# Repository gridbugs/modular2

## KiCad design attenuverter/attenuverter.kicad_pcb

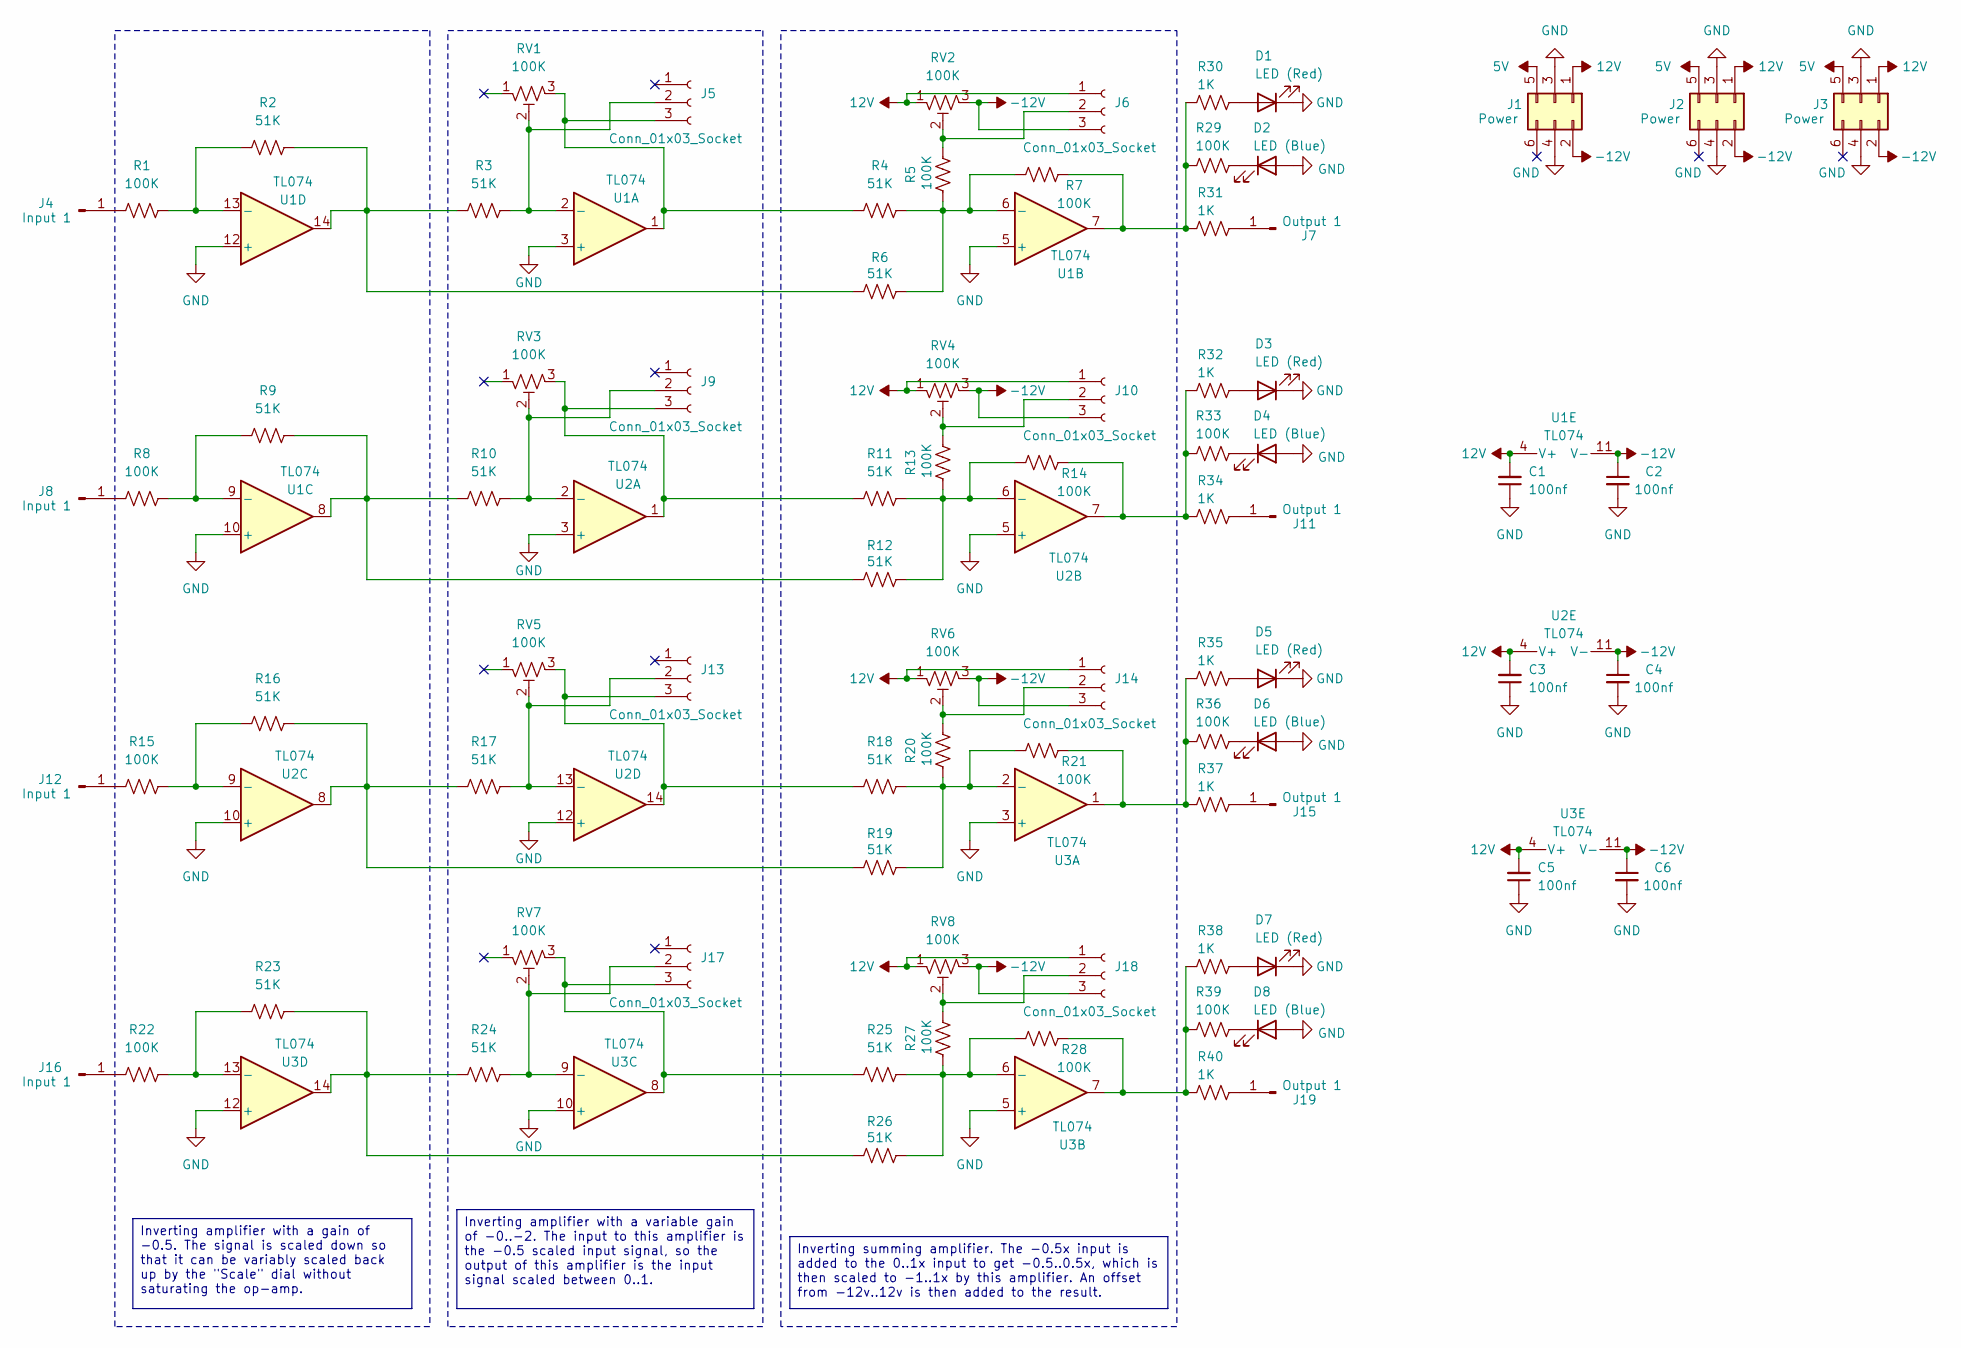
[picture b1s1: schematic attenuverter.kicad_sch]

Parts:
C1, C2, C3, C4, C5, C6: 100nf; C_Disc_D4.3mm_W1.9mm_P5.00mm
D1, D3, D5, D7: LED (Red); LED_D5.0mm
D2, D4, D6, D8: LED (Blue); LED_D5.0mm
J1, J2, J3: Power; IDC-Header_2x03_P2.54mm_Vertical
J4, J8, J12, J16: Input 1; banana-jack
J5, J6, J9, J10, J13, J14, J17, J18: Conn_01x03_Socket; pot
J7, J11, J15, J19: Output 1; banana-jack
R1, R5, R7, R8, R13, R14, R15, R20, R21, R22, R27, R28, R29, R33, R36, R39: 100K; R_Axial_DIN0207_L6.3mm_D2.5mm_P10.16mm_Horizontal
R2, R3, R4, R6, R9, R10, R11, R12, R16, R17, R18, R19, R23, R24, R25, R26: 51K; R_Axial_DIN0207_L6.3mm_D2.5mm_P10.16mm_Horizontal
R30, R31, R32, R34, R35, R37, R38, R40: 1K; R_Axial_DIN0207_L6.3mm_D2.5mm_P10.16mm_Horizontal
RV1, RV2, RV3, RV4, RV5, RV6, RV7, RV8: 100K; pot-socket
U1, U2, U3: TL074; DIP-14_W7.62mm_Socket

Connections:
5V: J1.5, J2.5, J3.5
12V: C1.2, C3.2, C5.2, J1.1, J2.1, J3.1, J6.1, J10.1, J14.1, J18.1, RV2.1, RV4.1, RV6.1, RV8.1, U1.4 (V+), U2.4 (V+), U3.4 (V+)
-12V: C2.1, C4.1, C6.1, J1.2, J2.2, J3.2, J6.3, J10.3, J14.3, J18.3, RV2.3, RV4.3, RV6.3, RV8.3, U1.11 (V-), U2.11 (V-), U3.11 (V-)
GND: C1.1, C2.2, C3.1, C4.2, C5.1, C6.2, D1.1 (K), D2.2 (A), D3.1 (K), D4.2 (A), D5.1 (K), D6.2 (A), D7.1 (K), D8.2 (A), J1.3, J1.4, J2.3, J2.4, J3.3, J3.4, U1.3 (+), U1.5 (+), U1.10 (+), U1.12 (+), U2.3 (+), U2.5 (+), U2.10 (+), U2.12 (+), U3.3 (+), U3.5 (+), U3.10 (+), U3.12 (+)
unnamed: D1.2 (A), R30.1
unnamed: D2.1 (K), R29.2
unnamed: D3.2 (A), R32.1
unnamed: D4.1 (K), R33.2
unnamed: D5.2 (A), R35.1
unnamed: D6.1 (K), R36.2
unnamed: D7.2 (A), R38.1
unnamed: D8.1 (K), R39.2
unnamed: J4.1, R1.1
unnamed: J5.2, R3.2, RV1.2, U1.2 (-)
unnamed: J5.3, R4.1, RV1.3, U1.1
unnamed: J6.2, R5.2, RV2.2
unnamed: J7.1, R31.1
unnamed: J8.1, R8.1
unnamed: J9.2, R10.2, RV3.2, U2.2 (-)
unnamed: J9.3, R11.1, RV3.3, U2.1
unnamed: J10.2, R13.2, RV4.2
unnamed: J11.1, R34.1
unnamed: J12.1, R15.1
unnamed: J13.2, R17.2, RV5.2, U2.13 (-)
unnamed: J13.3, R18.1, RV5.3, U2.14
unnamed: J14.2, R20.2, RV6.2
unnamed: J15.1, R37.1
unnamed: J16.1, R22.1
unnamed: J17.2, R24.2, RV7.2, U3.9 (-)
unnamed: J17.3, R25.1, RV7.3, U3.8
unnamed: J18.2, R27.2, RV8.2
unnamed: J19.1, R40.1
unnamed: R2.2, R3.1, R6.1, U1.14
unnamed: R9.2, R10.1, R12.1, U1.8
unnamed: R14.2, R32.2, R33.1, R34.2, U2.7
unnamed: R16.2, R17.1, R19.1, U2.8
unnamed: R21.2, R35.2, R36.1, R37.2, U3.1
unnamed: R23.2, R24.1, R26.1, U3.14
unnamed: R28.2, R38.2, R39.1, R40.2, U3.7
unnamed: R7.2, R29.1, R30.2, R31.2, U1.7
unnamed: R4.2, R5.1, R6.2, R7.1, U1.6 (-)
unnamed: R8.2, R9.1, U1.9 (-)
unnamed: R1.2, R2.1, U1.13 (-)
unnamed: R11.2, R12.2, R13.1, R14.1, U2.6 (-)
unnamed: R15.2, R16.1, U2.9 (-)
unnamed: R18.2, R19.2, R20.1, R21.1, U3.2 (-)
unnamed: R25.2, R26.2, R27.1, R28.1, U3.6 (-)
unnamed: R22.2, R23.1, U3.13 (-)

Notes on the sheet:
Inverting amplifier with a variable gain of -0..-2. The input to this amplifier is the -0.5 scaled input signal, so the output of this amplifier is the input signal scaled between 0..1.
Inverting amplifier with a gain of -0.5. The signal is scaled down so that it can be variably scaled back up by the "Scale" dial without saturating the op-amp.
Inverting summing amplifier. The -0.5x input is added to the 0..1x input to get -0.5..0.5x, which is then scaled to -1..1x by this amplifier. An offset from -12v..12v is then added to the result.

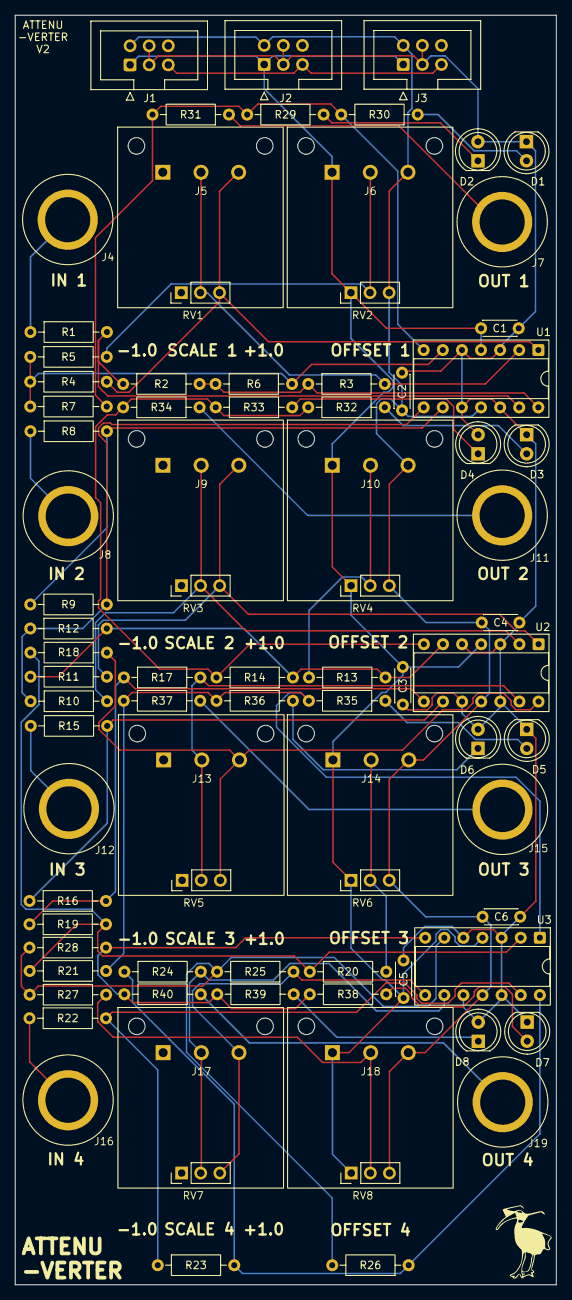
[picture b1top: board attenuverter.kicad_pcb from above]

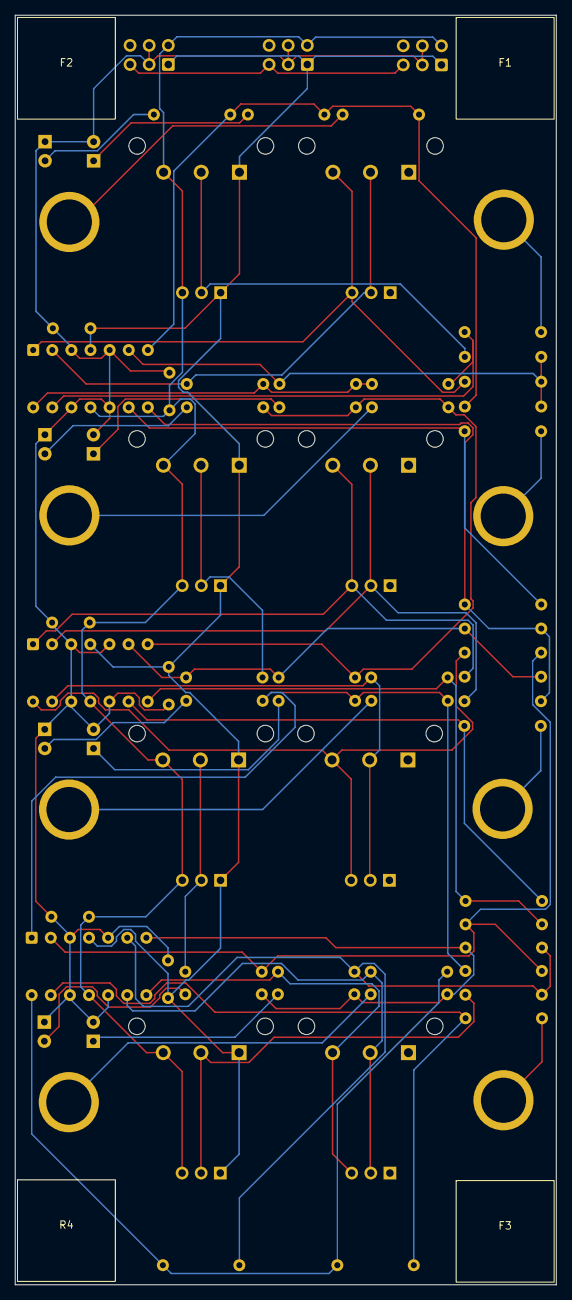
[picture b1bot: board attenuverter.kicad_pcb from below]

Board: 2 copper layers, 71.9 x 168.7 mm, 88 parts (4 on the bottom side), 48 nets.

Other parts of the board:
F1, F2, F3: foot
R4#2: foot

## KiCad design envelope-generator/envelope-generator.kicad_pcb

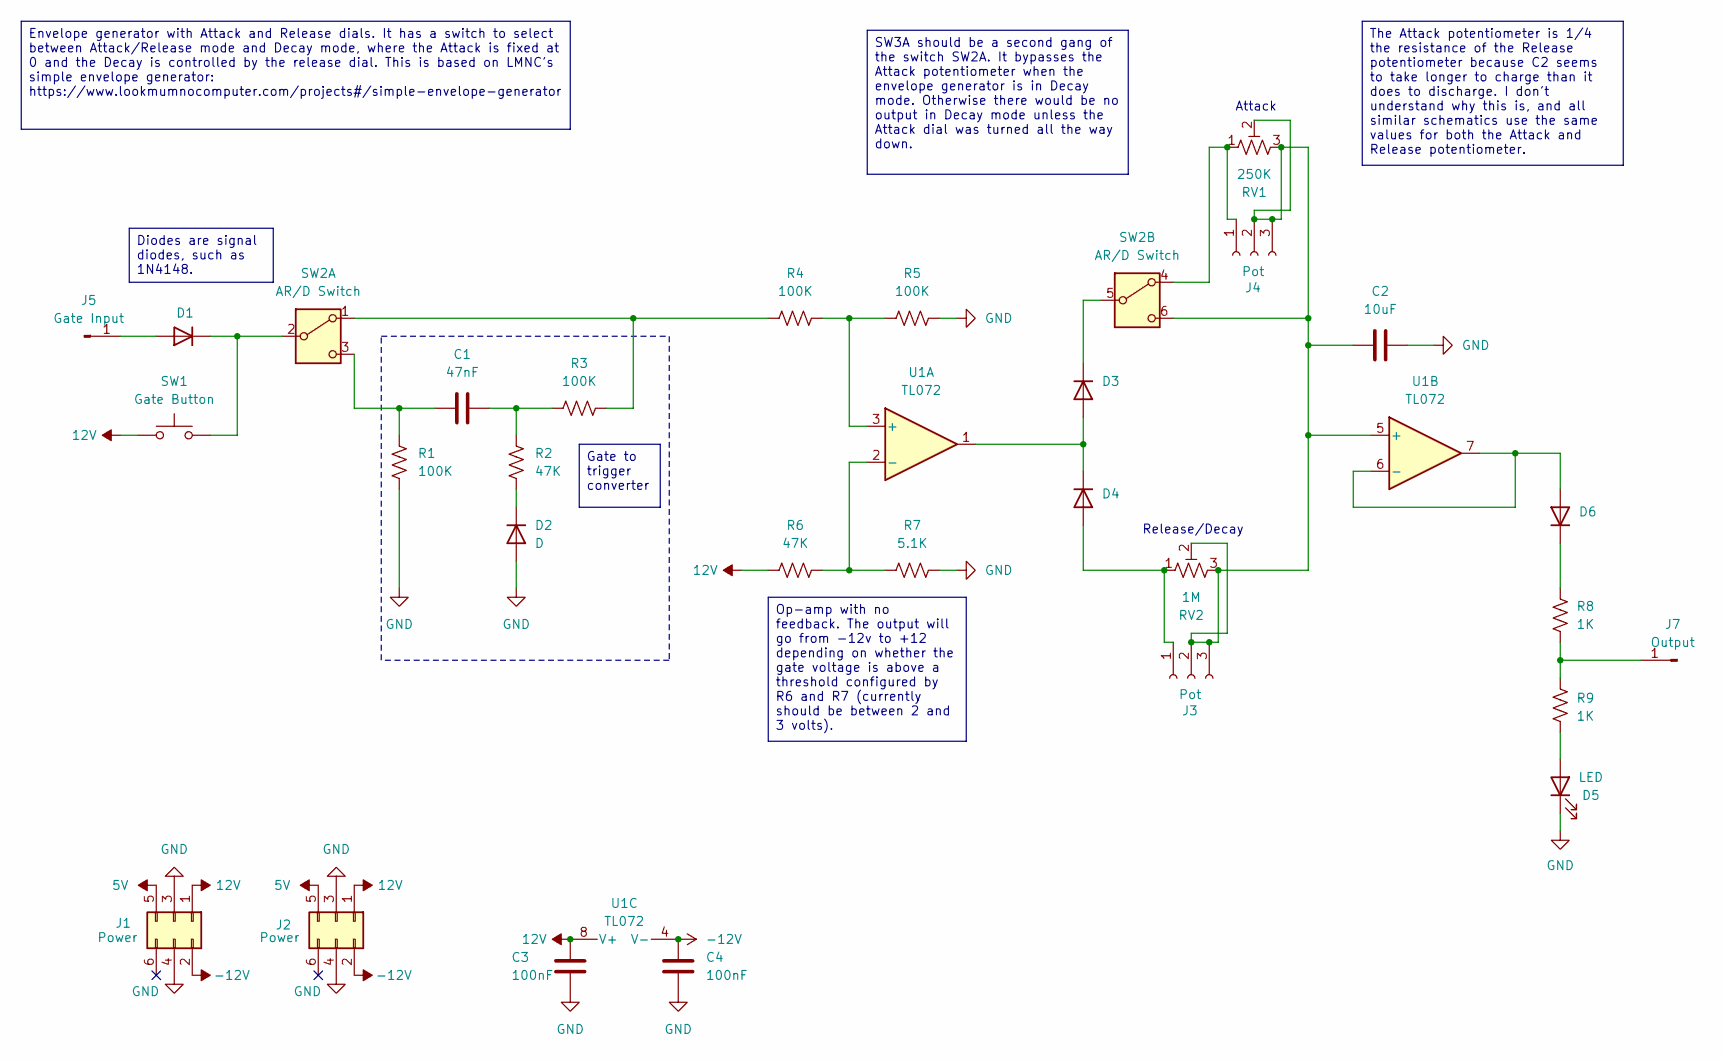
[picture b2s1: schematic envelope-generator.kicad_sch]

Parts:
C1: 47nF; C_Disc_D4.3mm_W1.9mm_P5.00mm
C2: 10uF; C_Disc_D4.3mm_W1.9mm_P5.00mm
C3, C4: 100nF; C_Disc_D4.3mm_W1.9mm_P5.00mm
D1, D2, D3: D; D_A-405_P7.62mm_Horizontal
D4, D6: D_A-405_P7.62mm_Horizontal
D5: LED; LED_D5.0mm
J1, J2: Power; IDC-Header_2x03_P2.54mm_Vertical
J3, J4: Pot; pot
J5: Gate Input; banana-jack
J7: Output; banana-jack
R1, R3, R4, R5: 100K; R_Axial_DIN0207_L6.3mm_D2.5mm_P10.16mm_Horizontal
R2, R6: 47K; R_Axial_DIN0207_L6.3mm_D2.5mm_P10.16mm_Horizontal
R7: 5.1K; R_Axial_DIN0207_L6.3mm_D2.5mm_P10.16mm_Horizontal
R8, R9: 1K; R_Axial_DIN0207_L6.3mm_D2.5mm_P10.16mm_Horizontal
RV1: 250K; pot-socket
RV2: 1M; pot-socket
SW1: Gate Button; SW_Cherry_MX_1.00u_PCB
SW2: AR/D Switch; switch2
U1: TL072; DIP-8_W7.62mm_Socket

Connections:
5V: J1.5, J2.5
12V: C3.2, J1.1, J2.1, R6.2, SW1.1, U1.8 (V+)
-12V: C4.2, J1.2, J2.2, U1.4 (V-)
GND: C2.2, C3.1, C4.1, D2.2 (A), D5.1 (K), J1.3, J1.4, J2.3, J2.4, R1.1, R5.1, R7.1
unnamed: C1.2, R2.2, R3.2
unnamed: D1.2 (A), J5.1
unnamed: D1.1 (K), SW1.2, SW2.2 (B)
unnamed: D2.1 (K), R2.1
unnamed: D3.2 (A), D4.1 (K), U1.1
unnamed: D3.1 (K), SW2.5 (B)
unnamed: D4.2 (A), J3.1, RV2.1
unnamed: D5.2 (A), R9.1
unnamed: D6.2 (A), U1.6 (-), U1.7
unnamed: D6.1 (K), R8.2
unnamed: C2.1, J3.2, J3.3, J4.2, J4.3, RV1.2, RV1.3, RV2.2, RV2.3, SW2.6 (C), U1.5 (+)
unnamed: J4.1, RV1.1, SW2.4 (A)
unnamed: J7.1, R8.1, R9.2
unnamed: R3.1, R4.2, SW2.1 (A)
unnamed: C1.1, R1.2, SW2.3 (C)
unnamed: R4.1, R5.2, U1.3 (+)
unnamed: R6.1, R7.2, U1.2 (-)

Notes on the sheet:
Attack
Release/Decay
SW3A should be a second gang of the switch SW2A. It bypasses the Attack potentiometer when the envelope generator is in Decay mode. Otherwise there would be no output in Decay mode unless the Attack dial was turned all the way down.
Diodes are signal diodes, such as 1N4148.
Envelope generator with Attack and Release dials. It has a switch to select between Attack/Release mode and Decay mode, where the Attack is fixed at 0 and the Decay is controlled by the release dial. This is based on LMNC's simple envelope generator: https://www.lookmumnocomputer.com/projects#/simp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
Gate to trigger converter
The Attack potentiometer is 1/4 the resistance of the Release potentiometer because C2 seems to take longer to charge than it does to discharge. I don't understand why this is, and all similar schematics use the same values for both the Attack and Release potentiometer.
Op-amp with no feedback. The output will go from -12v to +12 depending on whether the gate voltage is above a threshold configured by R6 and R7 (currently should be between 2 and 3 volts).

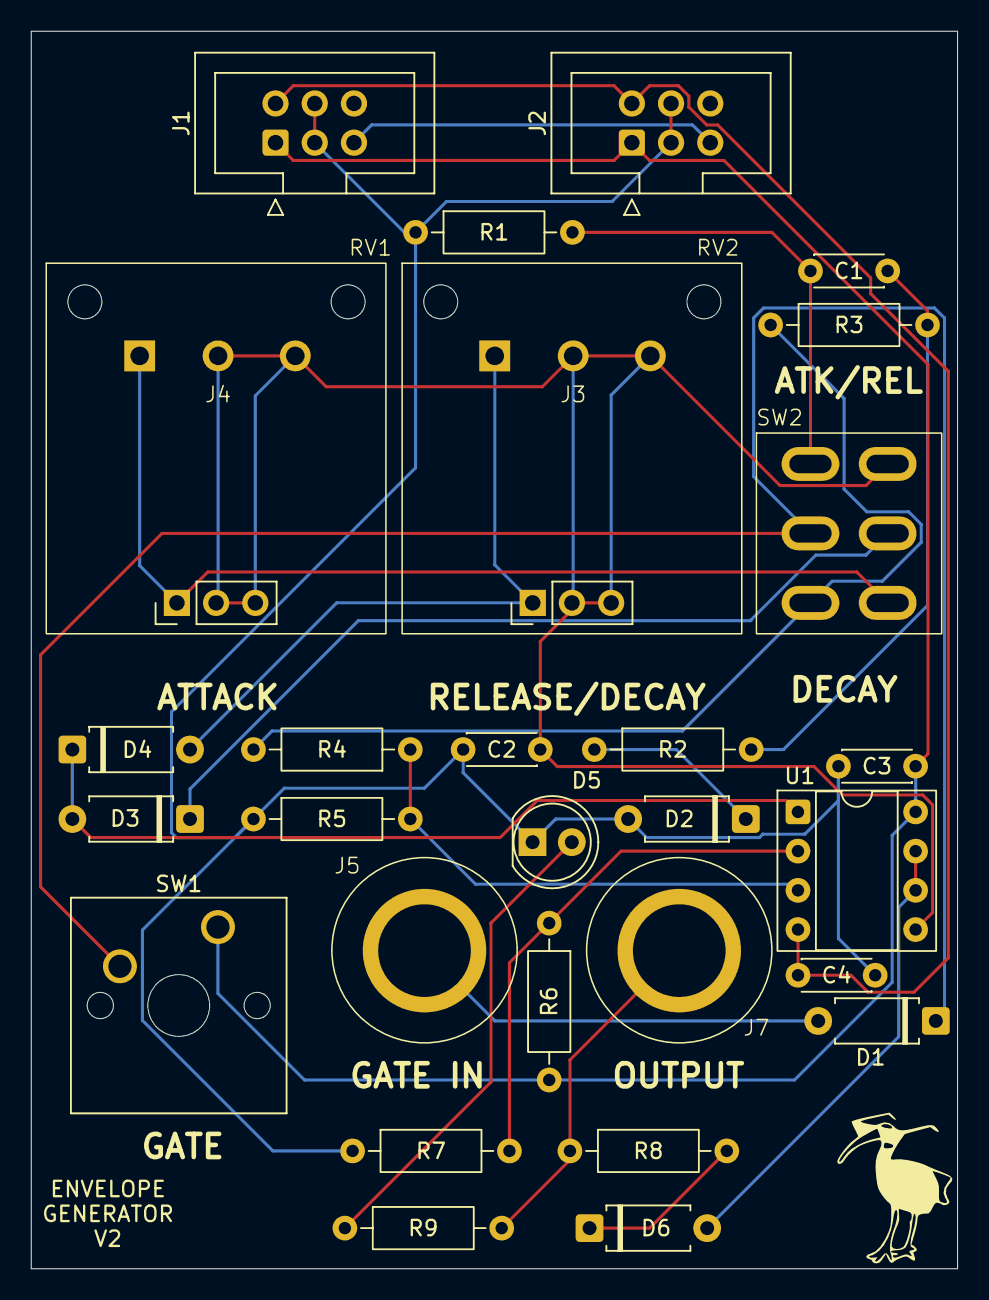
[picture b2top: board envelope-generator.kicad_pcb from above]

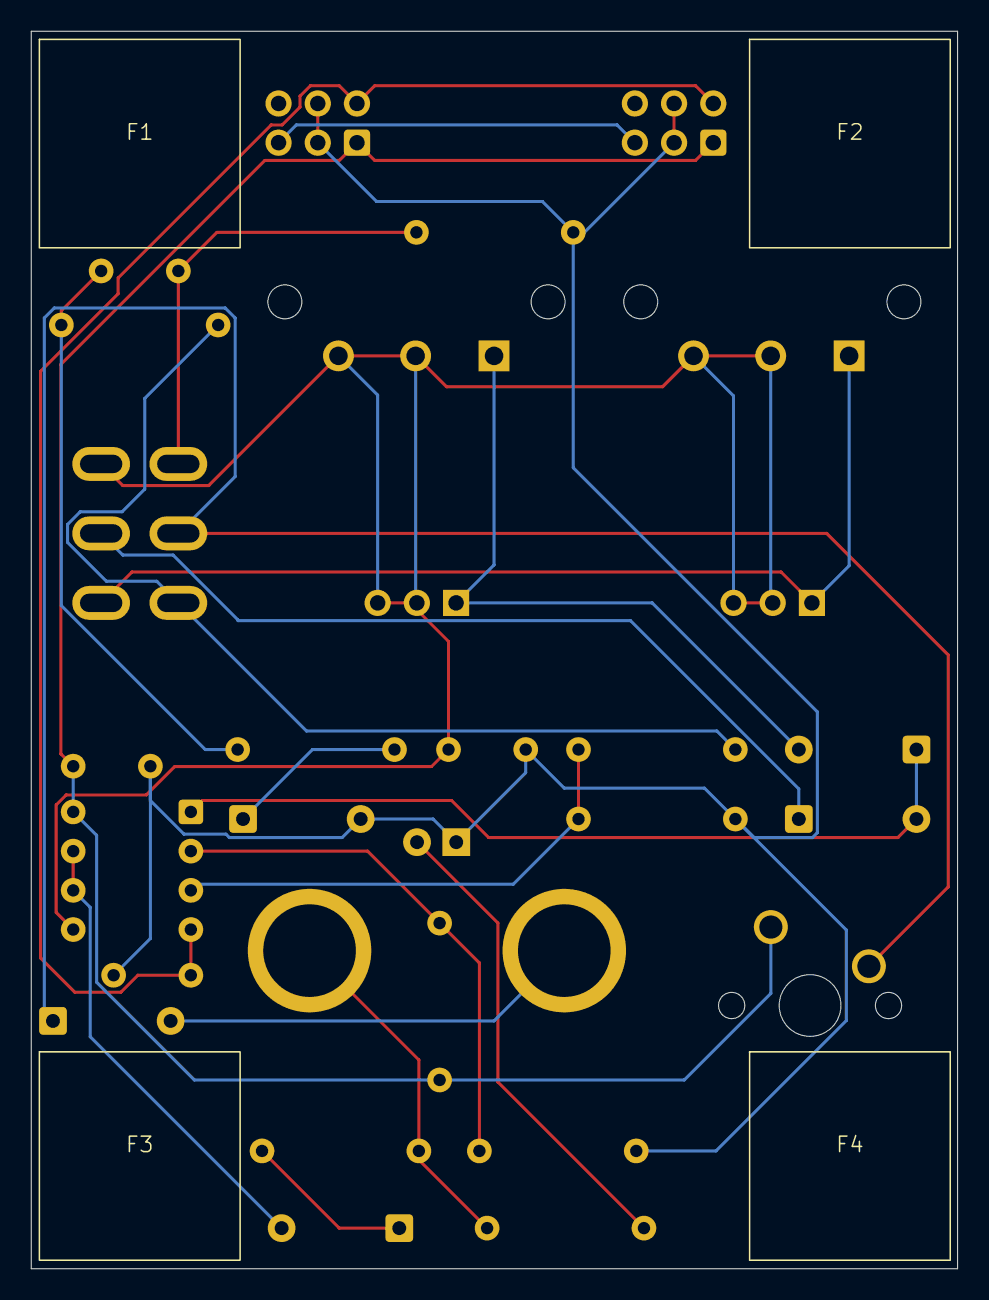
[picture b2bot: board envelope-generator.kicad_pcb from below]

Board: 2 copper layers, 60.0 x 80.2 mm, 34 parts (4 on the bottom side), 21 nets.

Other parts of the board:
F1, F2, F3, F4: foot

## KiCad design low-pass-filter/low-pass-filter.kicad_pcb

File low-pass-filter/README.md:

# Low-pass Filter

## Quirks

### V1

- The "Cutoff" potentiometer is reversed.

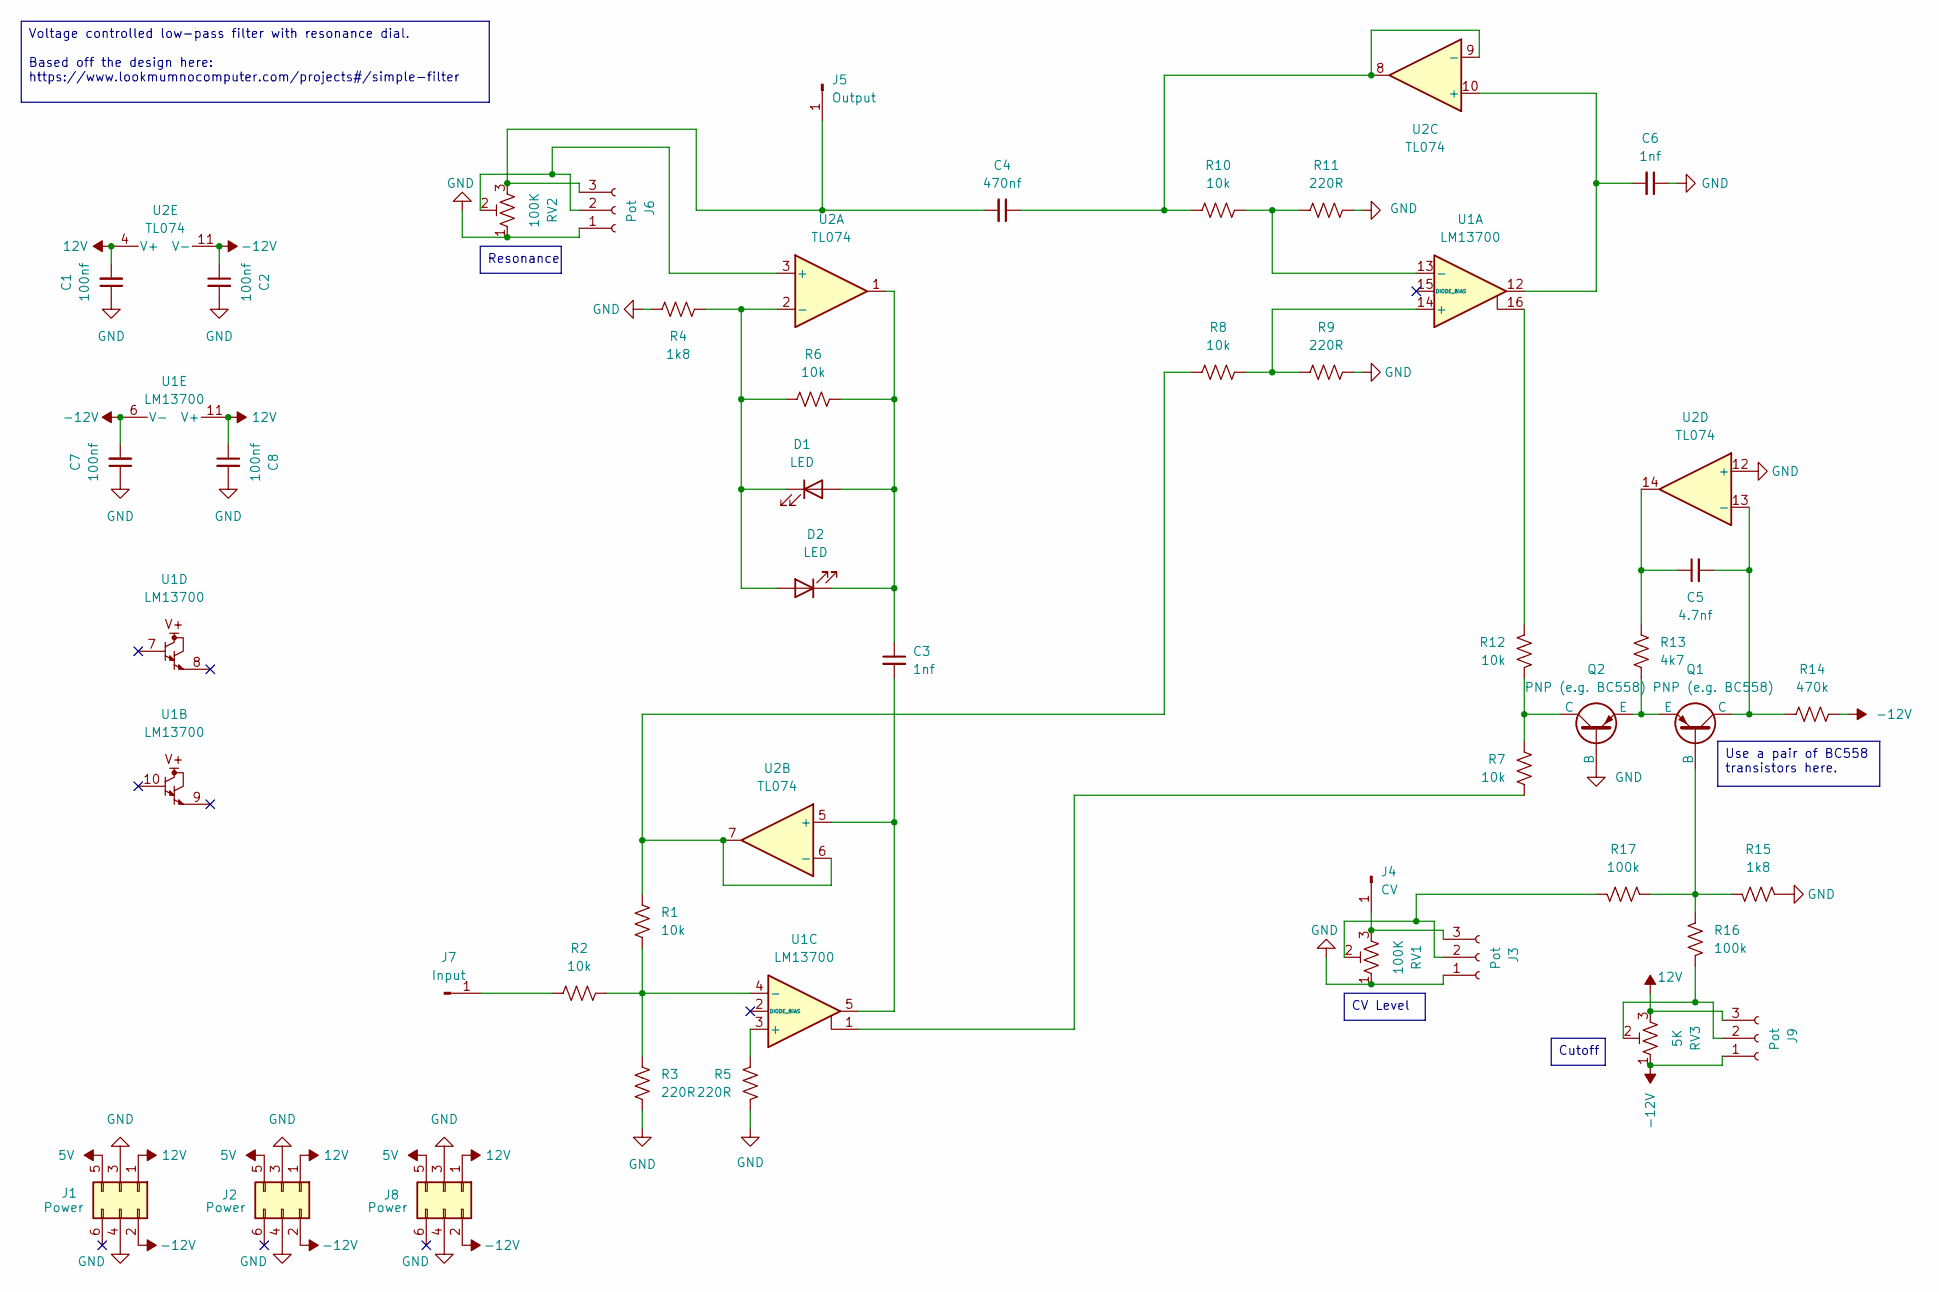
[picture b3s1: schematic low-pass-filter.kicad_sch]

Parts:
C1, C2, C7, C8: 100nf; C_Disc_D4.3mm_W1.9mm_P5.00mm
C3, C6: 1nf; C_Disc_D4.3mm_W1.9mm_P5.00mm
C4: 470nf; C_Disc_D4.3mm_W1.9mm_P5.00mm
C5: 4.7nf; C_Disc_D4.3mm_W1.9mm_P5.00mm
D1, D2: LED; LED_D5.0mm
J1, J2, J8: Power; IDC-Header_2x03_P2.54mm_Vertical
J3, J6, J9: Pot; pot
J4: CV; banana-jack
J5: Output; banana-jack
J7: Input; banana-jack
Q1, Q2: PNP (e.g. BC558); TO-92
R1, R2, R6, R7, R8, R10, R12: 10k; R_Axial_DIN0207_L6.3mm_D2.5mm_P10.16mm_Horizontal
R3, R5, R9, R11: 220R; R_Axial_DIN0207_L6.3mm_D2.5mm_P10.16mm_Horizontal
R4, R15: 1k8; R_Axial_DIN0207_L6.3mm_D2.5mm_P10.16mm_Horizontal
R13: 4k7; R_Axial_DIN0207_L6.3mm_D2.5mm_P10.16mm_Horizontal
R14: 470k; R_Axial_DIN0207_L6.3mm_D2.5mm_P10.16mm_Horizontal
R16, R17: 100k; R_Axial_DIN0207_L6.3mm_D2.5mm_P10.16mm_Horizontal
RV1, RV2: 100K; pot-socket
RV3: 5K; pot-socket
U1: LM13700; DIP-16_W7.62mm_Socket
U2: TL074; DIP-14_W7.62mm_Socket

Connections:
5V: J1.5, J2.5, J8.5
12V: C1.2, C8.1, J1.1, J2.1, J8.1, J9.3, RV3.3, U1.11 (V+), U2.4 (V+)
-12V: C2.1, C7.2, J1.2, J2.2, J8.2, J9.1, R14.2, RV3.1, U1.6 (V-), U2.11 (V-)
GND: C1.1, C2.2, C6.1, C7.1, C8.2, J1.3, J1.4, J2.3, J2.4, J3.1, J6.1, J8.3, J8.4, Q2.2 (B), R3.2, R4.2, R5.1, R9.2, R11.2, R15.1, RV1.1, RV2.1, U2.12 (+)
unnamed: C5.1, R13.2, U2.14
unnamed: C3.1, D1.2 (A), D2.1 (K), R6.1, U2.1
unnamed: D1.1 (K), D2.2 (A), R4.1, R6.2, U2.2 (-)
unnamed: J3.2, R17.1, RV1.2
unnamed: J3.3, J4.1, RV1.3
unnamed: C4.2, J5.1, J6.3, RV2.3
unnamed: J6.2, RV2.2, U2.3 (+)
unnamed: J7.1, R2.2
unnamed: J9.2, R16.2, RV3.2
unnamed: Q1.2 (B), R15.2, R16.1, R17.2
unnamed: C5.2, Q1.1 (C), R14.1, U2.13 (-)
unnamed: Q1.3 (E), Q2.3 (E), R13.1
unnamed: Q2.1 (C), R7.1, R12.1
unnamed: R7.2, U1.1
unnamed: R12.2, U1.16
unnamed: R8.2, R9.1, U1.14 (+)
unnamed: R10.1, R11.1, U1.13 (-)
unnamed: R5.2, U1.3 (+)
unnamed: R1.2, R2.1, R3.1, U1.4 (-)
unnamed: C3.2, U1.5, U2.5 (+)
unnamed: R1.1, R8.1, U2.6 (-), U2.7
unnamed: C6.2, U1.12, U2.10 (+)
unnamed: C4.1, R10.2, U2.8, U2.9 (-)

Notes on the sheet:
Resonance
CV Level
Use a pair of BC558 transistors here.
Cutoff
Voltage controlled low-pass filter with resonance dial. Based off the design here: https://www.lookmumnocomputer.com/projects#/simple-filter

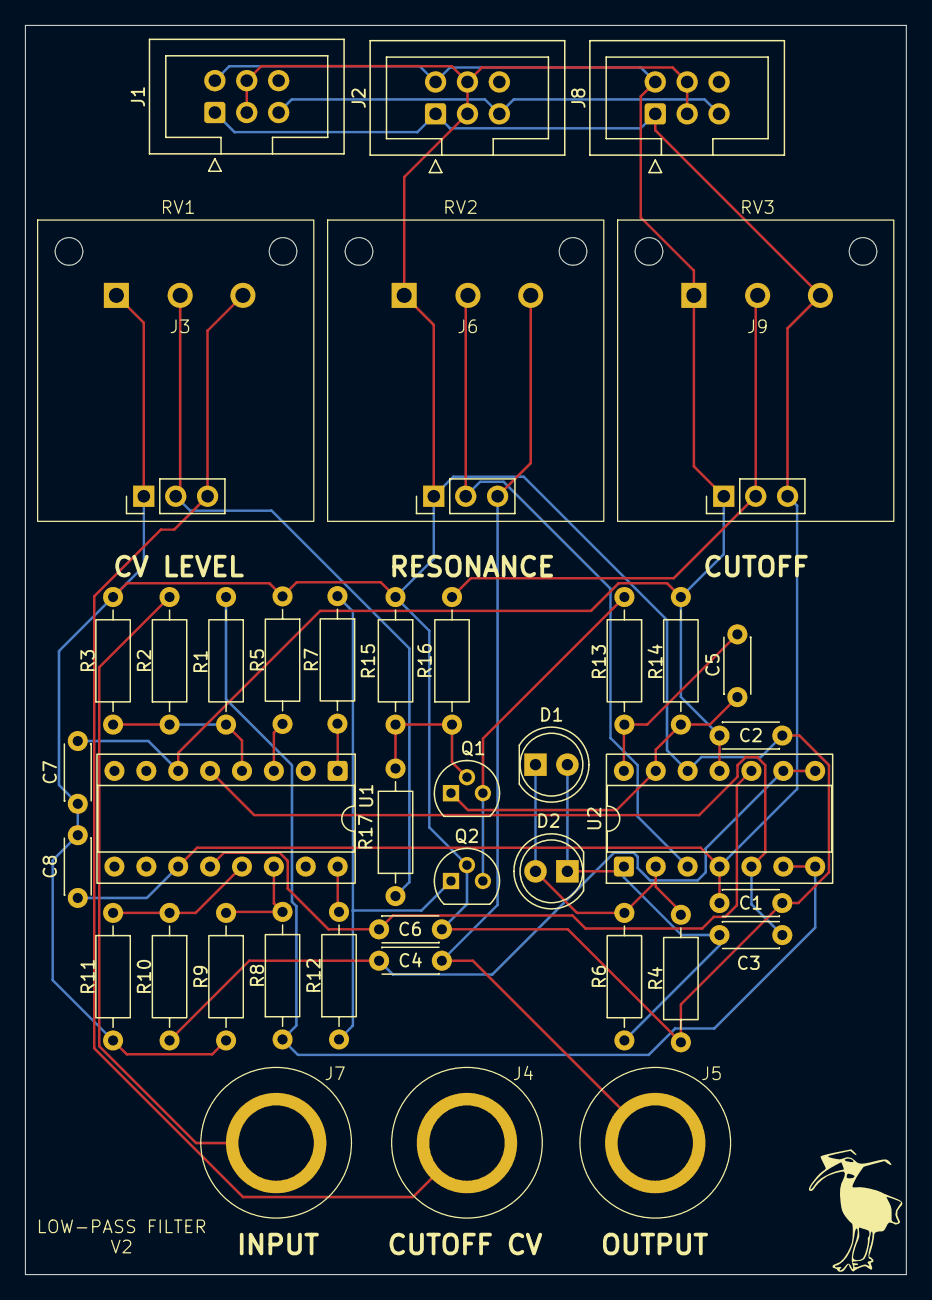
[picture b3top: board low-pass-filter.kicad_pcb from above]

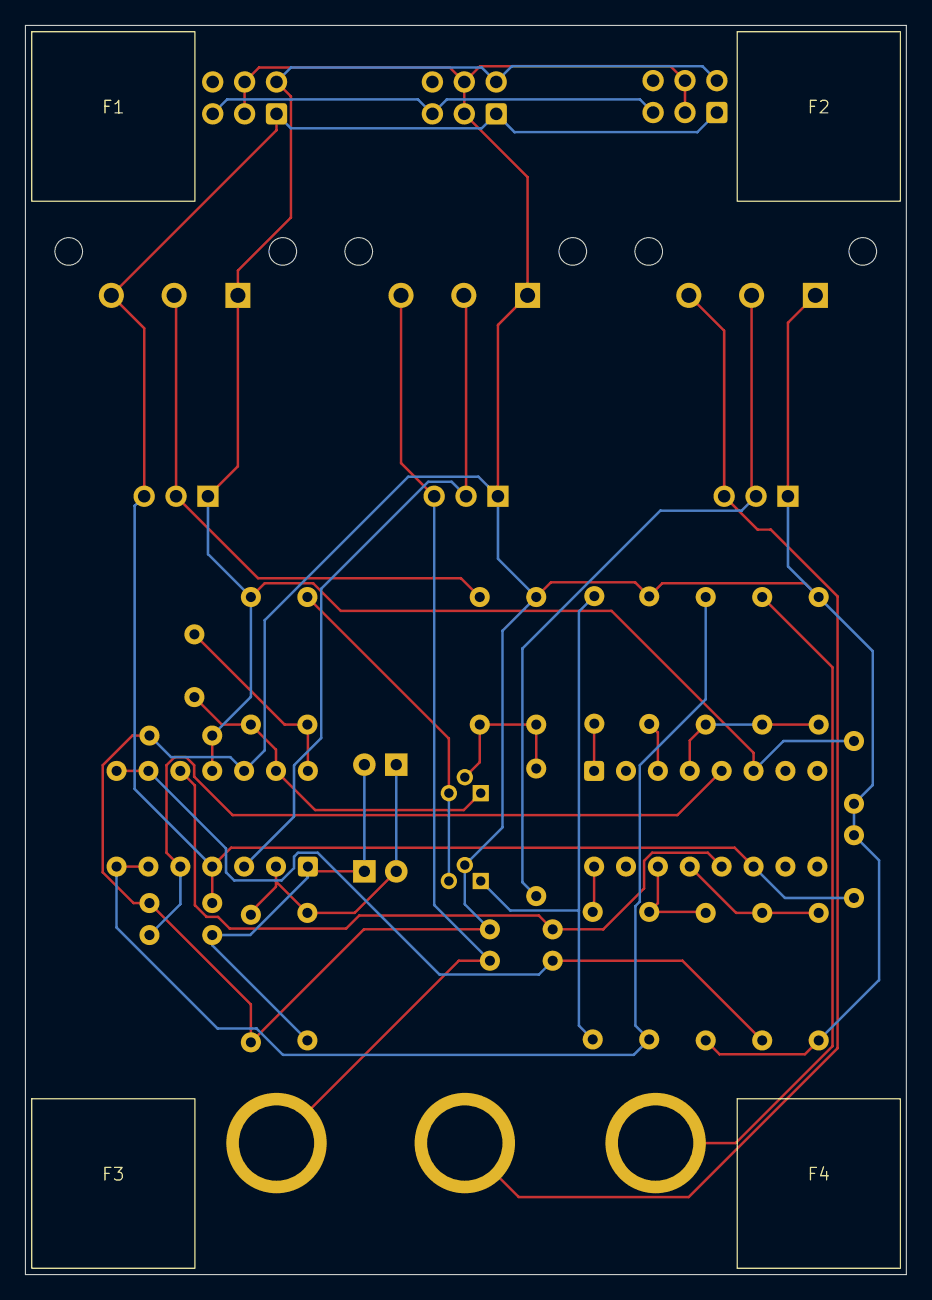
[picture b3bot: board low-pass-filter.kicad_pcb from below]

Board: 2 copper layers, 70.2 x 99.5 mm, 47 parts (4 on the bottom side), 27 nets.

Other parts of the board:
F1, F2, F3, F4: foot
